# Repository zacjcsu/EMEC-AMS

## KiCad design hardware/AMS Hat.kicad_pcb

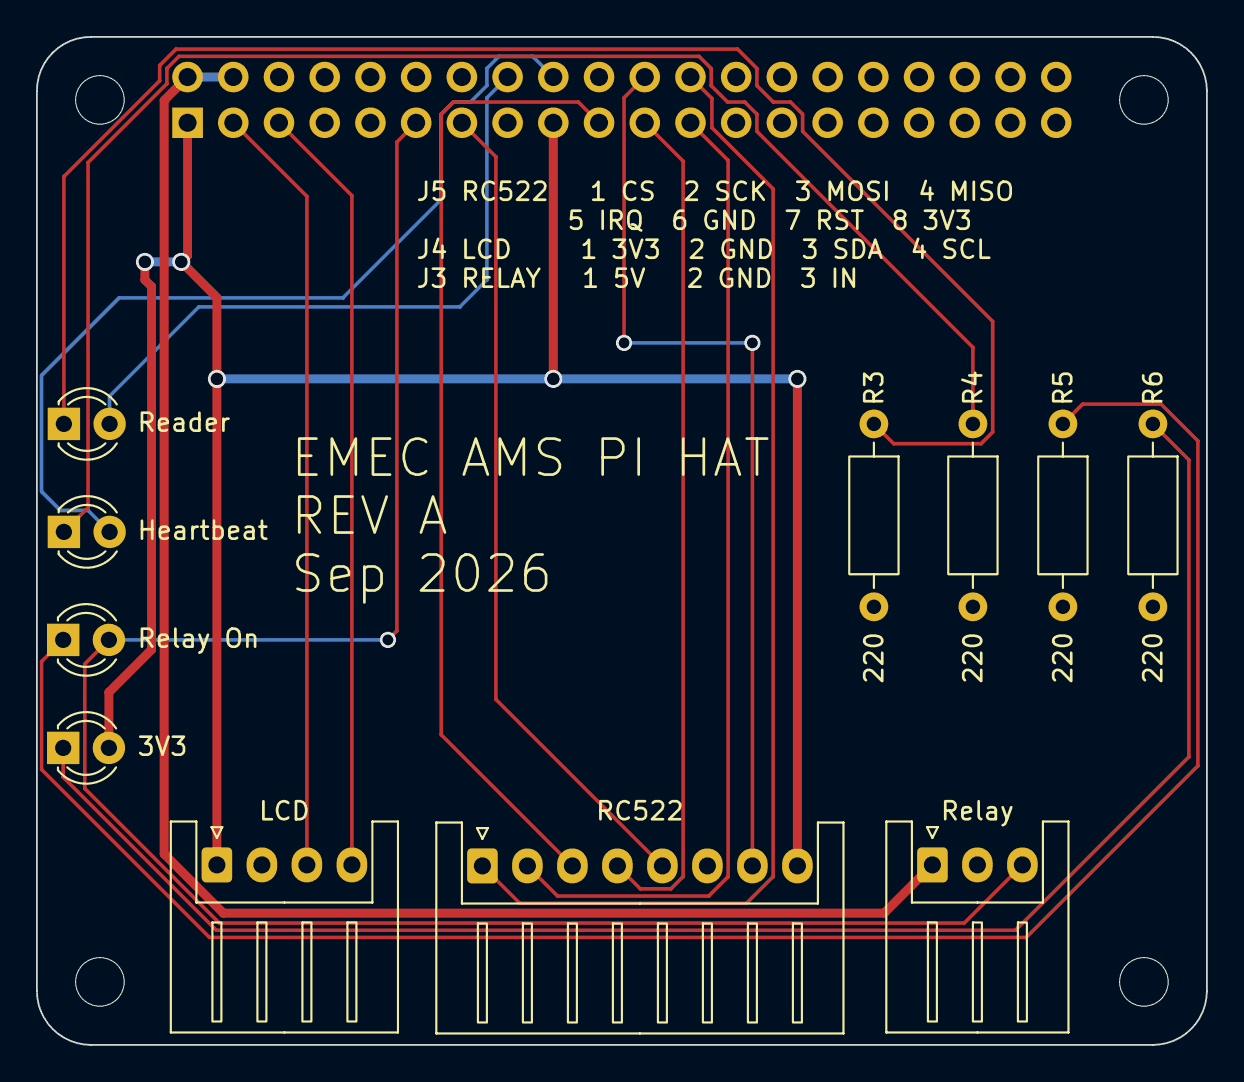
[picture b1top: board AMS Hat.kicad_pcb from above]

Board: 2 copper layers, 65.0 x 56.0 mm, 16 parts (1 on the bottom side), 18 nets.

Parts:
D1, D2, D3, D4: LED; LED_D3.0mm
J1: GPIO; PinSocket_2x20_P2.54mm_Vertical
J3: Relay; JST_XH_S3B-XH-A_1x03_P2.50mm_Horizontal
J4: LCD; JST_XH_S4B-XH-A_1x04_P2.50mm_Horizontal
J5: RC522; JST_XH_S8B-XH-A_1x08_P2.50mm_Horizontal
MH1, MH2, MH3, MH4: MountingHole_2.7mm_M2.5
R3, R4, R5, R6: 220; R_Axial_DIN0207_L6.3mm_D2.5mm_P10.16mm_Horizontal

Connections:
+3.3V: D4.2 (A), J1.1, J1.17, J4.1, J5.8
+5V: J1.2, J1.4, J3.1
GND: J1.6, J1.9, J1.14, J1.20, J1.25, J1.30, J1.34, J1.39, J3.2, J4.2, J5.6, R3.2, R4.2, R5.2, R6.2
LED_HEARTBEAT: D2.2 (A), J1.18
LED_READER: D1.2 (A), J1.16
unnamed: D1.1 (K), R3.1
unnamed: D2.1 (K), R4.1
unnamed: D3.1 (K), R5.1
unnamed: D4.1 (K), R6.1
RELAY_IN: D3.2 (A), J1.11, J3.3
RFID_CS-SDA: J1.24, J5.1
RFID_IRQ: J1.13, J5.5
RFID_MISO: J1.21, J5.4
RFID_MOSI: J1.19, J5.3
RFID_RST: J1.22, J5.7
RFID_SCK: J1.23, J5.2
SCL: J1.5, J4.4
SDA: J1.3, J4.3
